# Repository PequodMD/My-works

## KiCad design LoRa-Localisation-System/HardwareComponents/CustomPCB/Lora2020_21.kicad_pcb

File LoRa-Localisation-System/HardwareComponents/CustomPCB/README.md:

the PCB is used to provide circuit connection, debuging and addressing function  
design of PCB is done by [KiCAD](https://kicad.org/)  
[**ALL** project files for KiCAD](Lora2020_21.zip)  
[schematic file](Lora2020_21.sch)  
  
[circuit layout file](Lora2020_21.kicad_pcb)  
  
[gerber and drill files](Lora2020_21-gerbers3.zip)  
  
[Video for learning how to use KiCAD](https://www.youtube.com/watch?v=vaCVh2SAZY4)  
appearance of the board  

___
components on top:  
 + 2 LEDs and resistors(for debuging)
 + 6 ways DIP switch(to config address of the device)
 + a 5V to 3.3V regulator and two capacitors(power supply for Ra-02 module)
___
to fabricate the PCB, submit the GERBER files(Front and Bottom of copper, mask and silks layers) with the drill files(zip in one) to the following website  
[OSHPARK(for final PCB version)](https://oshpark.com/)  
[JLPCB(for prototype PCB)](https://jlcpcb.com/)

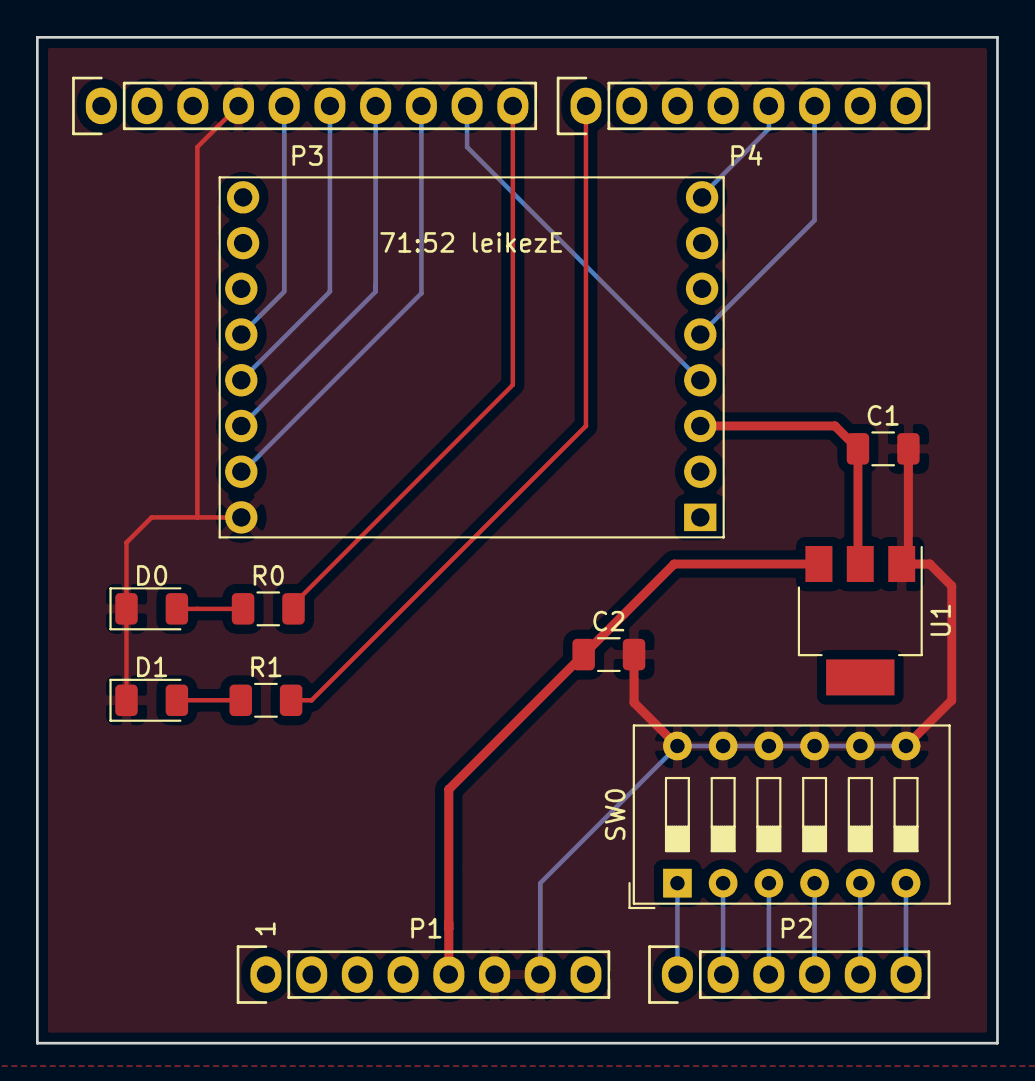
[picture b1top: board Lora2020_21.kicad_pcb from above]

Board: 2 copper layers, 53.3 x 55.9 mm, 13 parts (0 on the bottom side), 20 nets.

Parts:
71:52 leikezE: 71:52 leikezE; Ra-02(SX1278)
C1, C2: C_Small; C_1206_3216Metric
D0, D1: LED; LED_1206_3216Metric
P1: Power; Socket_Strip_Arduino_1x08
P2: Analog; Socket_Strip_Arduino_1x06
P3: Digital; Socket_Strip_Arduino_1x10
P4: Digital; Socket_Strip_Arduino_1x08
R0, R1: R; R_1206_3216Metric
SW0: SW_DIP_x06; SW_DIP_SPSTx06_Slide_9.78x17.42mm_W7.62mm_P2.54mm
U1: AMS1117-3.3; SOT-223-3_TabPin2

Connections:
2(DIO0): 71:52 leikezE.5, P4.6
3(DIO3): 71:52 leikezE.8, P4.5
9(RST): 71:52 leikezE.4, P3.9
10(NSS): 71:52 leikezE.15, P3.8
11(MOSI): 71:52 leikezE.14, P3.7
12(MISO): 71:52 leikezE.13, P3.6
13(SCK): 71:52 leikezE.12, P3.5
+5V: C2.1, P1.5, U1.3
GND: 71:52 leikezE.16, C1.2, C2.2, D0.1, D1.1, P1.6, P1.7, P3.4, SW0.7, SW0.8, SW0.9, SW0.10, SW0.11, SW0.12, U1.1
LED0: P3.10, R0.2
LED1: P4.1, R1.2
unnamed: 71:52 leikezE.3, C1.1, U1.2
unnamed: D0.2, R0.1
unnamed: D1.2, R1.1
S0: P2.1, SW0.1
S1: P2.2, SW0.2
S2: P2.3, SW0.3
S3: P2.4, SW0.4
S4: P2.5, P3.2, SW0.5
S5: P2.6, P3.1, SW0.6

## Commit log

2021-04-27 Create Software&Code
